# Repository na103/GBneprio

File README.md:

## GameBoy  compatible 2MB Flash Cart 
A classic Game Boy Cart with only a 2MB flash ROM, designed for low cost and low power consumption.</BR>
Derived from the MBC5/MBC1 hybrid by insideGadgets and adapted to the ATF1502 logic CPLD.
</BR></BR>

## Bill of materials
| Qt. |    Description     |             Designator          |    JLCPCB part     |        Mouser part            |
|:---:|--------------------|---------------------------------|--------------------|-------------------------------|
|3    |Capacitor 100nF     |C1,C2,C3                         |C106221             | CC0603ZRY5V9BB104             |
|1    |CPLD                |U1                               |C1521098            | ATF1502AS-10AU44              |
|2    |16Mbit Flash Rom    |U2                               |C1015902            | M29F160FT55N3E2               |

## Note

Please note that the PCB thickness must be 0.8mm.</br>
In the PCB Assembly folder, you can find the BOM and CPL files for production and assembly with JLCPCB.</br>
To program the CPLD, you will need a compatible JTAG programmer (e.g., Atmel ATDH1150USB) and the SKEDD connector from Wurth Elektronik (code 490107671012).</br>
When programming the CPLD from the JTAG connector, you must supply the board with 5V separately.</br>

If you found this my work useful, please consider buying me a cup of coffee if you want:<br>

## License

This work is licensed under a Creative Commons Attribution 4.0 International License. See [https://creativecommons.org/licenses/by/4.0/](https://creativecommons.org/licenses/by/4.0/).

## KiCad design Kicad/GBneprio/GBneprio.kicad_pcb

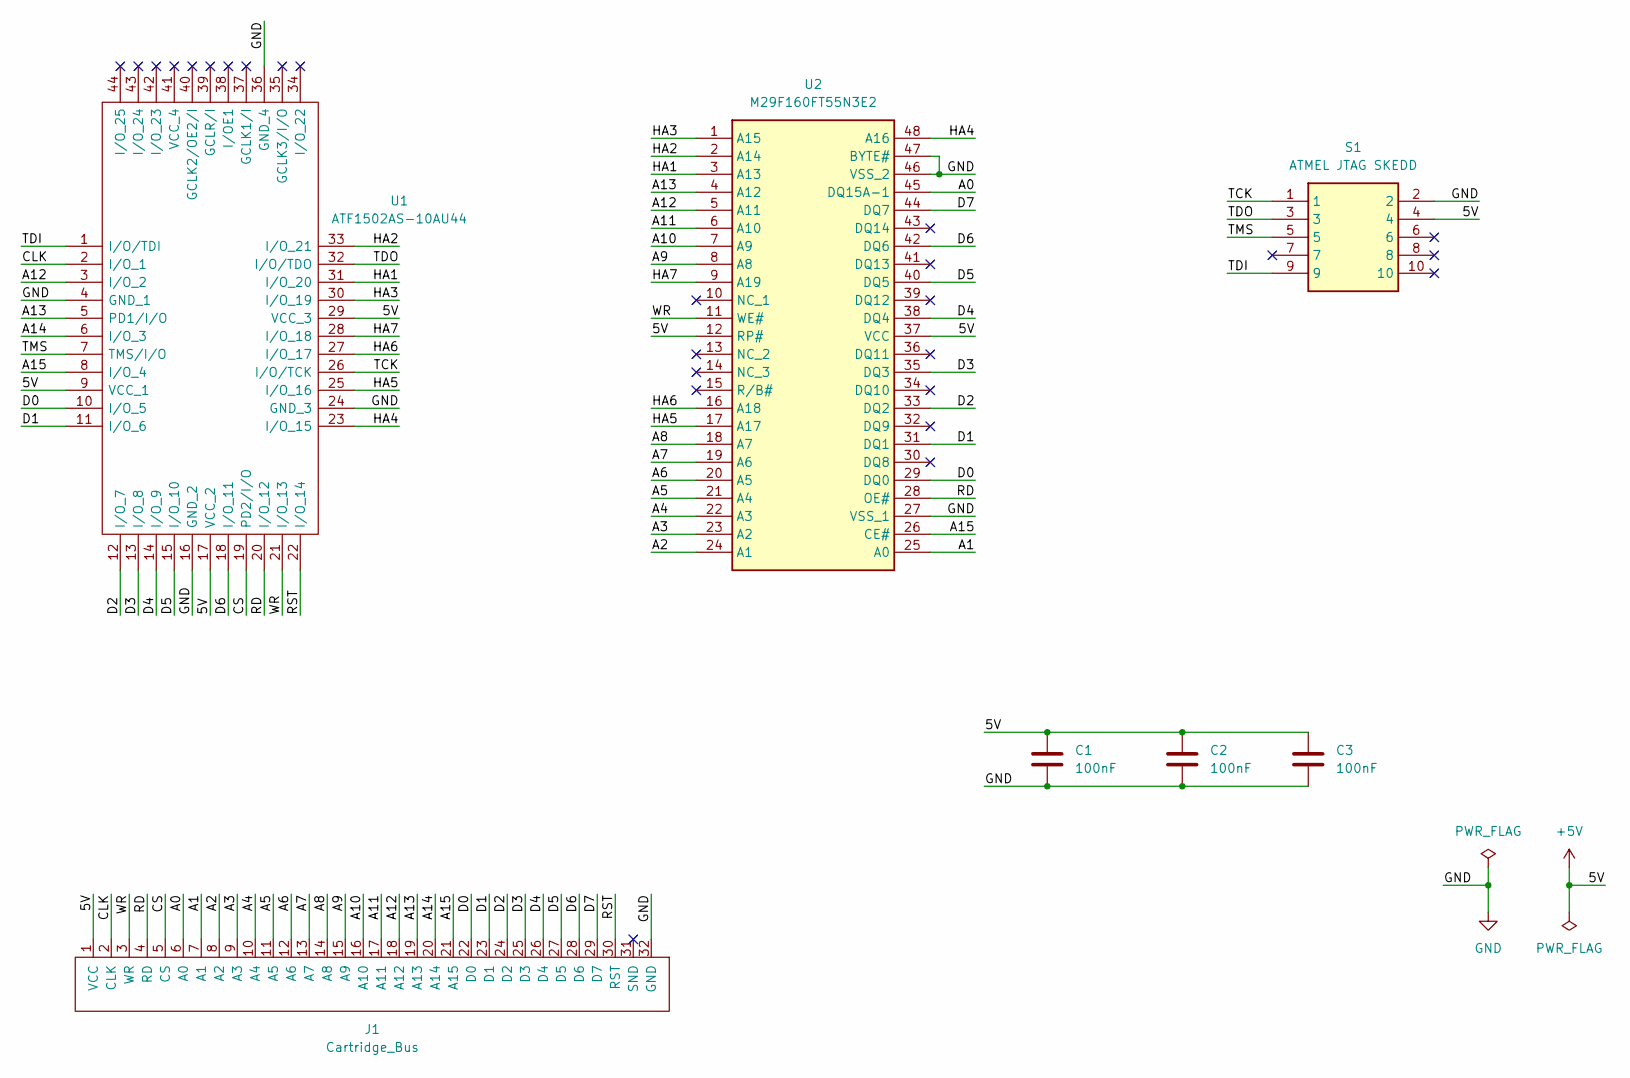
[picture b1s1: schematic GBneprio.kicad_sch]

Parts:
C1, C2, C3: 100nF; C_0603_1608Metric_Pad1.08x0.95mm_HandSolder
J1: Cartridge_Bus; GB_Cartridge
S1: ATMEL JTAG SKEDD; 490107671012; Mouser Part Number 710-490107671012
U1: ATF1502AS-10AU44; QFP80P1200X1200X120-44N; Mouser Part Number 556-AF1502AS10AU44
U2: M29F160FT55N3E2; SOP50P2000X120-48N; Mouser Part Number 913-M29F160FT55N3E2

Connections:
+5V: C1.1, C2.1, C3.1, J1.1 (VCC), S1.4, U1.9 (VCC_1), U1.17 (VCC_2), U1.29 (VCC_3), U2.12 (RP#), U2.37 (VCC)
/A0: J1.6 (A0), U2.45 (DQ15A-1)
/A1: J1.7 (A1), U2.25 (A0)
/A2: J1.8 (A2), U2.24 (A1)
/A3: J1.9 (A3), U2.23 (A2)
/A4: J1.10 (A4), U2.22 (A3)
/A5: J1.11 (A5), U2.21 (A4)
/A6: J1.12 (A6), U2.20 (A5)
/A7: J1.13 (A7), U2.19 (A6)
/A8: J1.14 (A8), U2.18 (A7)
/A9: J1.15 (A9), U2.8 (A8)
/A10: J1.16 (A10), U2.7 (A9)
/A11: J1.17 (A11), U2.6 (A10)
/A12: J1.18 (A12), U1.3 (I/O_2), U2.5 (A11)
/A13: J1.19 (A13), U1.5 (PD1/I/O), U2.4 (A12)
/A14: J1.20 (A14), U1.6 (I/O_3)
/A15: J1.21 (A15), U1.8 (I/O_4), U2.26 (CE#)
/CLK: J1.2 (CLK~), U1.2 (I/O_1)
/CS: J1.5 (CS), U1.19 (PD2/I/O)
/D0: J1.22 (D0), U1.10 (I/O_5), U2.29 (DQ0)
/D1: J1.23 (D1), U1.11 (I/O_6), U2.31 (DQ1)
/D2: J1.24 (D2), U1.12 (I/O_7), U2.33 (DQ2)
/D3: J1.25 (D3), U1.13 (I/O_8), U2.35 (DQ3)
/D4: J1.26 (D4), U1.14 (I/O_9), U2.38 (DQ4)
/D5: J1.27 (D5), U1.15 (I/O_10), U2.40 (DQ5)
/D6: J1.28 (D6), U1.18 (I/O_11), U2.42 (DQ6)
/D7: J1.29 (D7), U2.44 (DQ7)
/HA1: U1.31 (I/O_20), U2.3 (A13)
/HA2: U1.33 (I/O_21), U2.2 (A14)
/HA3: U1.30 (I/O_19), U2.1 (A15)
/HA4: U1.23 (I/O_15), U2.48 (A16)
/HA5: U1.25 (I/O_16), U2.17 (A17)
/HA6: U1.27 (I/O_17), U2.16 (A18)
/HA7: U1.28 (I/O_18), U2.9 (A19)
/RD: J1.4 (RD), U1.20 (I/O_12), U2.28 (OE#)
/RST: J1.30 (RST), U1.22 (I/O_14)
/TCK: S1.1, U1.26 (I/O/TCK)
/TDI: S1.9, U1.1 (I/O/TDI)
/TDO: S1.3, U1.32 (I/O/TDO)
/TMS: S1.5, U1.7 (TMS/I/O)
/WR: J1.3 (WR), U1.21 (I/O_13), U2.11 (WE#)
GND: C1.2, C2.2, C3.2, J1.32 (GND), S1.2, U1.4 (GND_1), U1.16 (GND_2), U1.24 (GND_3), U1.36 (GND_4), U2.27 (VSS_1), U2.46 (VSS_2), U2.47 (BYTE#)

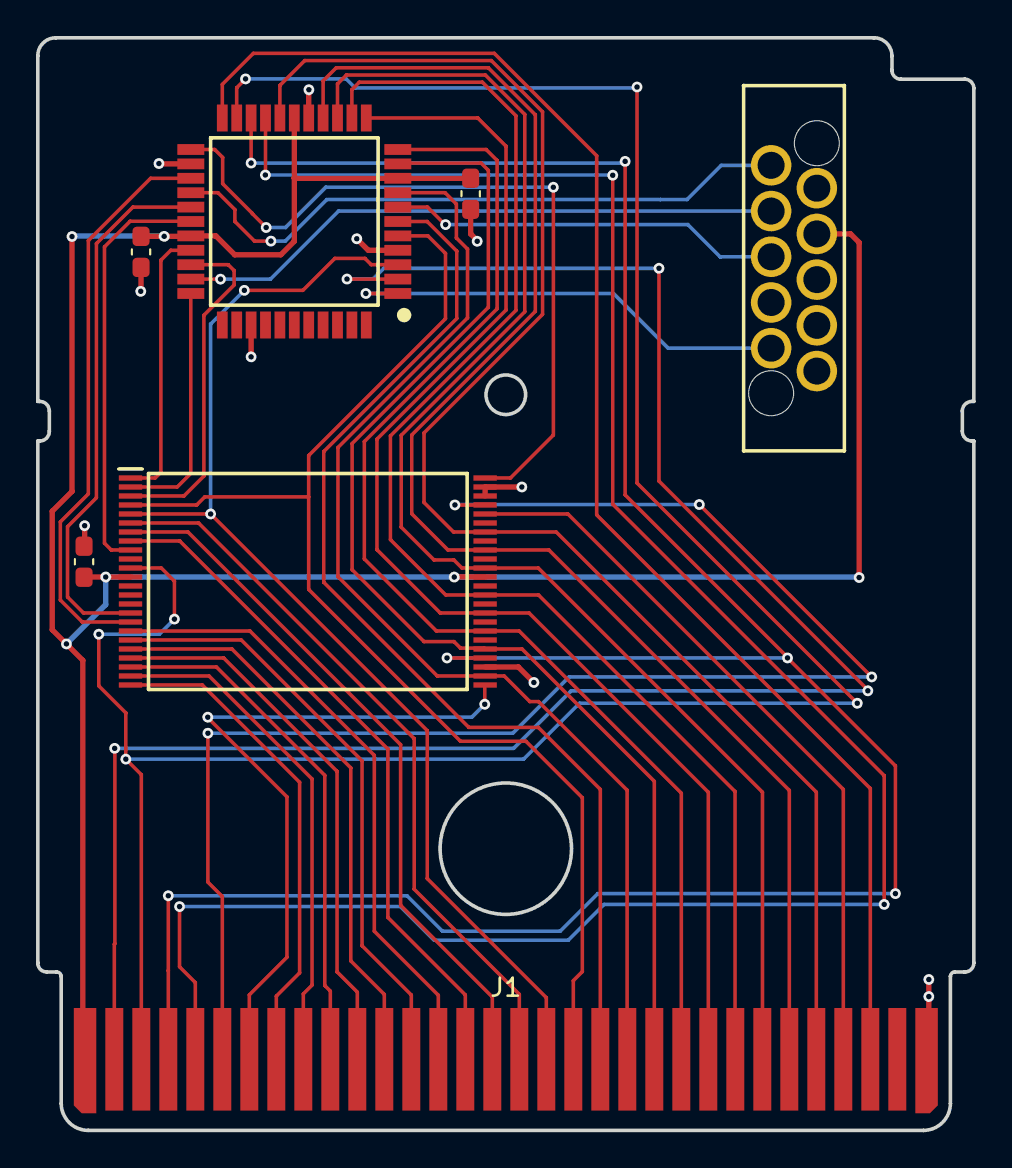
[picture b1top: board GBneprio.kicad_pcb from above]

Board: 2 copper layers, 52.0 x 60.7 mm, 7 parts (0 on the bottom side), 42 nets.

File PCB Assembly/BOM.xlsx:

Comment | Designator | Footprint | JLCPCB Part #（optional）
ATF1502AS-10AU44 | U1 | TQFP-44(10x10) | C1521098
M29F160FT55N3E2 | U2 | TSOP-48-12.0mm | C1015902
100nF | C1 | 0603 | C106221
100nF | C2 | 0603 | C106221
100nF | C3 | 0603 | C106221

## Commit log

2026-05-21 Create LICENSE
2026-05-21 kicad project
2026-05-21 assembly file
2026-05-21 Quartus project
